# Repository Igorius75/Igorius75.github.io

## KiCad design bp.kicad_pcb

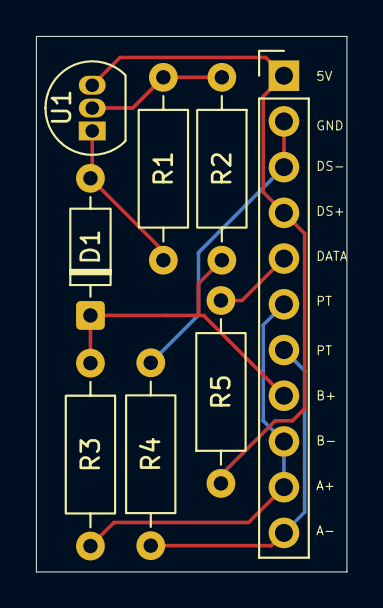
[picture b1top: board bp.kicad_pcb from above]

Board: 2 copper layers, 17.2 x 29.8 mm, 8 parts (0 on the bottom side), 8 nets.

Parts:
D1: 1N4148; D_DO-35_SOD27_P7.62mm_Horizontal
J5: Conn_01x11; PinHeader_1x11_P2.54mm_Vertical
R1: 860; R_Axial_DIN0207_L6.3mm_D2.5mm_P10.16mm_Horizontal
R2: 11k; R_Axial_DIN0207_L6.3mm_D2.5mm_P10.16mm_Horizontal
R3: 100; R_Axial_DIN0207_L6.3mm_D2.5mm_P10.16mm_Horizontal
R4: 15k; R_Axial_DIN0207_L6.3mm_D2.5mm_P10.16mm_Horizontal
R5: 4.7k; R_Axial_DIN0207_L6.3mm_D2.5mm_P10.16mm_Horizontal
U1: LM334Z; TO-92_Inline

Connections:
A-: J5.7, J5.11, R4.1
B+: D1.1 (K), J5.8, R2.2, R3.1
B-/A+: J5.6, J5.9, J5.10, R3.2
unnamed: D1.2 (A), R1.2, U1.1
unnamed: J5.1, J5.4, R5.1, U1.3
unnamed: J5.2, J5.3, R4.2
unnamed: J5.5, R5.2
unnamed: R1.1, R2.1, U1.2

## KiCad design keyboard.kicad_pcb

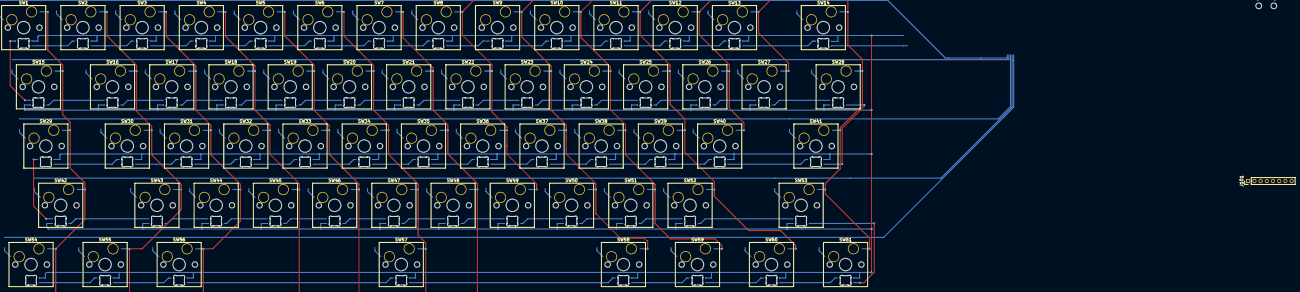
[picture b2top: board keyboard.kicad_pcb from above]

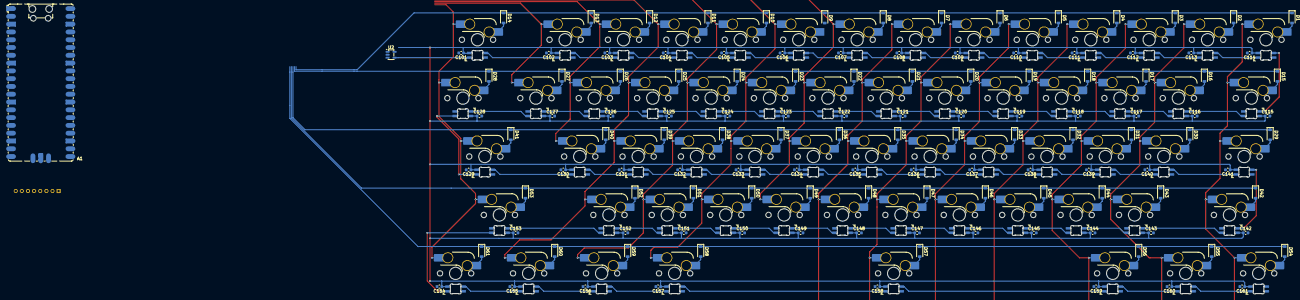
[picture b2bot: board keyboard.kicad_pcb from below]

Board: 2 copper layers, 247 parts (124 on the bottom side), 150 nets.

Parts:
A1: RaspberryPi_Pico; RaspberryPi_Pico_SMD_HandSolder
C101, C102, C103, C104, C105, C106, C107, C108, C109, C110, C111, C112, C113, C114, C115, C116, C117, C118, C119, C120, C121, C122, C123, C124, C125, C126, C127, C128, C129, C130, C131, C132, C133, C134, C135, C136, C137, C138, C139, C140, C141, C142, C143, C144, C145, C146, C147, C148, C149, C150, C151, C152, C153, C154, C155, C156, C157, C158, C159, C160, C161: 100nF; C_0603_1608Metric
D1, D2, D3, D4, D5, D6, D7, D8, D9, D10, D11, D12, D13, D14, D15, D16, D17, D18, D19, D20, D21, D22, D23, D24, D25, D26, D27, D28, D29, D30, D31, D32, D33, D34, D35, D36, D37, D38, D39, D40, D41, D42, D43, D44, D45, D46, D47, D48, D49, D50, D51, D52, D53, D54, D55, D56, D57, D58, D59, D60, D61: D; D_SOD-123
D101, D102, D103, D104, D105, D106, D107, D108, D109, D110, D111, D112, D113, D114, D129, D130, D131, D132, D133, D134, D135, D136, D137, D138, D139, D140, D141, D154, D155, D156, D157, D158, D159, D160, D161: SK6812MINI; MX_SK6812MINI-E
D115, D116, D117, D118, D119, D120, D121, D122, D123, D124, D125, D126, D127, D128, D142, D143, D144, D145, D146, D147, D148, D149, D150, D151, D152, D153: SK6812MINI; MX_SK6812MINI-E_REV
J101: ConnSPI; PinHeader_1x08_P2.00mm_Vertical
SW1, SW2, SW3, SW4, SW5, SW6, SW7, SW8, SW9, SW10, SW11, SW12, SW13, SW16, SW17, SW18, SW19, SW20, SW21, SW22, SW23, SW24, SW25, SW26, SW27, SW30, SW31, SW32, SW33, SW34, SW35, SW36, SW37, SW38, SW39, SW40, SW43, SW44, SW45, SW46, SW47, SW48, SW49, SW50, SW51, SW52: SW_Push; SW_Hotswap_Kailh_MX_Plated_1.00u
SW14: SW_Push; SW_Hotswap_Kailh_MX_Plated_2.00u
SW15, SW28: SW_Push; SW_Hotswap_Kailh_MX_Plated_1.50u
SW29: SW_Push; SW_Hotswap_Kailh_MX_Plated_1.75u
SW41, SW42: SW_Push; SW_Hotswap_Kailh_MX_Plated_2.25u
SW53: SW_Push; SW_Hotswap_Kailh_MX_Plated_2.75u
SW54, SW55, SW56, SW58, SW59, SW60, SW61: SW_Push; SW_Hotswap_Kailh_MX_Plated_1.25u
SW57: SW_Push; SW_Hotswap_Kailh_MX_Plated_6.25u
U2: SN74LV1T34DBV; SOT-23-5

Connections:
3V3: A1.36 (3V3), J101.1 (BLK), J101.7 (VCC)
C1: SW1.2, SW15.2, SW29.2, SW42.2, SW54.2
C2: SW2.2, SW16.2, SW30.2, SW43.2, SW55.2
C3: SW3.2, SW17.2, SW31.2, SW44.2, SW56.2
C4: SW4.2, SW18.2, SW32.2, SW45.2
C5: SW5.2, SW19.2, SW33.2, SW46.2
C6: SW6.2, SW20.2, SW34.2, SW47.2, SW57.2
C7: SW7.2, SW21.2, SW35.2, SW48.2
C8: SW8.2, SW22.2, SW36.2, SW49.2
C9: SW9.2, SW23.2, SW37.2, SW50.2, SW58.2
C10: SW10.2, SW24.2, SW38.2, SW51.2, SW59.2
C11: SW11.2, SW25.2, SW39.2, SW52.2, SW60.2
C12: SW12.2, SW26.2, SW40.2
C13: SW13.2, SW27.2
C14: SW14.2, SW28.2, SW41.2, SW53.2, SW61.2
GND: A1.3 (GND), A1.8 (GND), A1.13 (GND), A1.18 (GND), A1.23 (GND), A1.28 (GND), A1.38 (GND), A1.D2 (GND), C101.2, C102.2, C103.2, C104.2, C105.2, C106.2, C107.2, C108.2, C109.2, C110.2, C111.2, C112.2, C113.2, C114.2, C115.2, C116.2, C117.2, C118.2, C119.2, C120.2, C121.2, C122.2, C123.2, C124.2, C125.2, C126.2, C127.2, C128.2, C129.2, C130.2, C131.2, C132.2, C133.2, C134.2, C135.2, C136.2, C137.2, C138.2, C139.2, C140.2, C141.2, C142.2, C143.2, C144.2, C145.2, C146.2, C147.2, C148.2, C149.2, C150.2, C151.2, C152.2, C153.2, C154.2, C155.2, C156.2, C157.2, C158.2, C159.2, C160.2, C161.2, D101.2 (VSS), D102.2 (VSS), D103.2 (VSS), D104.2 (VSS), D105.2 (VSS), D106.2 (VSS), D107.2 (VSS), D108.2 (VSS), D109.2 (VSS), D110.2 (VSS), D111.2 (VSS), D112.2 (VSS), D113.2 (VSS), D114.2 (VSS), D115.2 (VSS), D116.2 (VSS), D117.2 (VSS), D118.2 (VSS), D119.2 (VSS), D120.2 (VSS), D121.2 (VSS), D122.2 (VSS), D123.2 (VSS), D124.2 (VSS), D125.2 (VSS), D126.2 (VSS), D127.2 (VSS), D128.2 (VSS), D129.2 (VSS), D130.2 (VSS), D131.2 (VSS), D132.2 (VSS), D133.2 (VSS), D134.2 (VSS), D135.2 (VSS), D136.2 (VSS), D137.2 (VSS), D138.2 (VSS), D139.2 (VSS), D140.2 (VSS), D141.2 (VSS), D142.2 (VSS), D143.2 (VSS), D144.2 (VSS), D145.2 (VSS), D146.2 (VSS), D147.2 (VSS), D148.2 (VSS), D149.2 (VSS), D150.2 (VSS), D151.2 (VSS), D152.2 (VSS), D153.2 (VSS), D154.2 (VSS), D155.2 (VSS), D156.2 (VSS), D157.2 (VSS), D158.2 (VSS), D159.2 (VSS), D160.2 (VSS), D161.2 (VSS), J101.8 (GND), U2.3 (GND)
LEDdata: D101.3 (DIN), U2.4 (Y)
unnamed: A1.12 (GPIO9), U2.2 (A)
unnamed: A1.14 (GPIO10), J101.6 (SCL)
unnamed: A1.15 (GPIO11), J101.5 (SDA)
unnamed: A1.16 (GPIO12), J101.3 (DC)
unnamed: A1.17 (GPIO13), J101.2 (CS)
unnamed: A1.19 (GPIO14), J101.4 (RES)
unnamed: D1.2 (A), SW1.1
unnamed: D2.2 (A), SW2.1
unnamed: D3.2 (A), SW3.1
unnamed: D4.2 (A), SW4.1
unnamed: D5.2 (A), SW5.1
unnamed: D6.2 (A), SW6.1
unnamed: D7.2 (A), SW7.1
unnamed: D8.2 (A), SW8.1
unnamed: D9.2 (A), SW9.1
unnamed: D10.2 (A), SW10.1
unnamed: D11.2 (A), SW11.1
unnamed: D12.2 (A), SW12.1
unnamed: D13.2 (A), SW13.1
unnamed: D14.2 (A), SW14.1
unnamed: D15.2 (A), SW15.1
unnamed: D16.2 (A), SW16.1
unnamed: D17.2 (A), SW17.1
unnamed: D18.2 (A), SW18.1
unnamed: D19.2 (A), SW19.1
unnamed: D20.2 (A), SW20.1
unnamed: D21.2 (A), SW21.1
unnamed: D22.2 (A), SW22.1
unnamed: D23.2 (A), SW23.1
unnamed: D24.2 (A), SW24.1
unnamed: D25.2 (A), SW25.1
unnamed: D26.2 (A), SW26.1
unnamed: D27.2 (A), SW27.1
unnamed: D28.2 (A), SW28.1
unnamed: D29.2 (A), SW29.1
unnamed: D30.2 (A), SW30.1
unnamed: D31.2 (A), SW31.1
unnamed: D32.2 (A), SW32.1
unnamed: D33.2 (A), SW33.1
unnamed: D34.2 (A), SW34.1
unnamed: D35.2 (A), SW35.1
unnamed: D36.2 (A), SW36.1
unnamed: D37.2 (A), SW37.1
unnamed: D38.2 (A), SW38.1
unnamed: D39.2 (A), SW39.1
unnamed: D40.2 (A), SW40.1
unnamed: D41.2 (A), SW41.1
unnamed: D42.2 (A), SW42.1
unnamed: D43.2 (A), SW43.1
unnamed: D44.2 (A), SW44.1
unnamed: D45.2 (A), SW45.1
unnamed: D46.2 (A), SW46.1
unnamed: D47.2 (A), SW47.1
unnamed: D48.2 (A), SW48.1
unnamed: D49.2 (A), SW49.1
unnamed: D50.2 (A), SW50.1
unnamed: D51.2 (A), SW51.1
unnamed: D52.2 (A), SW52.1
unnamed: D53.2 (A), SW53.1
unnamed: D54.2 (A), SW54.1
unnamed: D55.2 (A), SW55.1
unnamed: D56.2 (A), SW56.1
unnamed: D57.2 (A), SW57.1
unnamed: D58.2 (A), SW58.1
unnamed: D59.2 (A), SW59.1
unnamed: D60.2 (A), SW60.1
unnamed: D61.2 (A), SW61.1
unnamed: D101.1 (DOUT), D102.3 (DIN)
unnamed: D102.1 (DOUT), D103.3 (DIN)
unnamed: D103.1 (DOUT), D104.3 (DIN)
unnamed: D104.1 (DOUT), D105.3 (DIN)
unnamed: D105.1 (DOUT), D106.3 (DIN)
unnamed: D106.1 (DOUT), D107.3 (DIN)
unnamed: D107.1 (DOUT), D108.3 (DIN)
unnamed: D108.1 (DOUT), D109.3 (DIN)
unnamed: D109.1 (DOUT), D110.3 (DIN)
unnamed: D110.1 (DOUT), D111.3 (DIN)
unnamed: D111.1 (DOUT), D112.3 (DIN)
unnamed: D112.1 (DOUT), D113.3 (DIN)
unnamed: D113.1 (DOUT), D114.3 (DIN)
unnamed: D114.1 (DOUT), D115.3 (DIN)
unnamed: D115.1 (DOUT), D116.3 (DIN)
unnamed: D116.1 (DOUT), D117.3 (DIN)
unnamed: D117.1 (DOUT), D118.3 (DIN)
unnamed: D118.1 (DOUT), D119.3 (DIN)
unnamed: D119.1 (DOUT), D120.3 (DIN)
unnamed: D120.1 (DOUT), D121.3 (DIN)
unnamed: D121.1 (DOUT), D122.3 (DIN)
unnamed: D122.1 (DOUT), D123.3 (DIN)
unnamed: D123.1 (DOUT), D124.3 (DIN)
unnamed: D124.1 (DOUT), D125.3 (DIN)
unnamed: D125.1 (DOUT), D126.3 (DIN)
unnamed: D126.1 (DOUT), D127.3 (DIN)
unnamed: D127.1 (DOUT), D128.3 (DIN)
unnamed: D128.1 (DOUT), D129.3 (DIN)
unnamed: D129.1 (DOUT), D130.3 (DIN)
unnamed: D130.1 (DOUT), D131.3 (DIN)
unnamed: D131.1 (DOUT), D132.3 (DIN)
unnamed: D132.1 (DOUT), D133.3 (DIN)
unnamed: D133.1 (DOUT), D134.3 (DIN)
unnamed: D134.1 (DOUT), D135.3 (DIN)
unnamed: D135.1 (DOUT), D136.3 (DIN)
unnamed: D136.1 (DOUT), D137.3 (DIN)
unnamed: D137.1 (DOUT), D138.3 (DIN)
unnamed: D138.1 (DOUT), D139.3 (DIN)
unnamed: D139.1 (DOUT), D140.3 (DIN)
unnamed: D140.1 (DOUT), D141.3 (DIN)
unnamed: D141.1 (DOUT), D142.3 (DIN)
unnamed: D142.1 (DOUT), D143.3 (DIN)
unnamed: D143.1 (DOUT), D144.3 (DIN)
unnamed: D144.1 (DOUT), D145.3 (DIN)
unnamed: D145.1 (DOUT), D146.3 (DIN)
unnamed: D146.1 (DOUT), D147.3 (DIN)
unnamed: D147.1 (DOUT), D148.3 (DIN)
unnamed: D148.1 (DOUT), D149.3 (DIN)
unnamed: D149.1 (DOUT), D150.3 (DIN)
unnamed: D150.1 (DOUT), D151.3 (DIN)
unnamed: D151.1 (DOUT), D152.3 (DIN)
unnamed: D152.1 (DOUT), D153.3 (DIN)
unnamed: D153.1 (DOUT), D154.3 (DIN)
unnamed: D154.1 (DOUT), D155.3 (DIN)
unnamed: D155.1 (DOUT), D156.3 (DIN)
unnamed: D156.1 (DOUT), D157.3 (DIN)
unnamed: D157.1 (DOUT), D158.3 (DIN)
unnamed: D158.1 (DOUT), D159.3 (DIN)
unnamed: D159.1 (DOUT), D160.3 (DIN)
unnamed: D160.1 (DOUT), D161.3 (DIN)
R1: D1.1 (K), D2.1 (K), D3.1 (K), D4.1 (K), D5.1 (K), D6.1 (K), D7.1 (K), D8.1 (K), D9.1 (K), D10.1 (K), D11.1 (K), D12.1 (K), D13.1 (K), D14.1 (K)
R2: D15.1 (K), D16.1 (K), D17.1 (K), D18.1 (K), D19.1 (K), D20.1 (K), D21.1 (K), D22.1 (K), D23.1 (K), D24.1 (K), D25.1 (K), D26.1 (K), D27.1 (K), D28.1 (K)
R3: D29.1 (K), D30.1 (K), D31.1 (K), D32.1 (K), D33.1 (K), D34.1 (K), D35.1 (K), D36.1 (K), D37.1 (K), D38.1 (K), D39.1 (K), D40.1 (K), D41.1 (K)
R4: D42.1 (K), D43.1 (K), D44.1 (K), D45.1 (K), D46.1 (K), D47.1 (K), D48.1 (K), D49.1 (K), D50.1 (K), D51.1 (K), D52.1 (K), D53.1 (K)
R5: D54.1 (K), D55.1 (K), D56.1 (K), D57.1 (K), D58.1 (K), D59.1 (K), D60.1 (K), D61.1 (K)
Vсс: A1.40 (VBUS), C101.1, C102.1, C103.1, C104.1, C105.1, C106.1, C107.1, C108.1, C109.1, C110.1, C111.1, C112.1, C113.1, C114.1, C115.1, C116.1, C117.1, C118.1, C119.1, C120.1, C121.1, C122.1, C123.1, C124.1, C125.1, C126.1, C127.1, C128.1, C129.1, C130.1, C131.1, C132.1, C133.1, C134.1, C135.1, C136.1, C137.1, C138.1, C139.1, C140.1, C141.1, C142.1, C143.1, C144.1, C145.1, C146.1, C147.1, C148.1, C149.1, C150.1, C151.1, C152.1, C153.1, C154.1, C155.1, C156.1, C157.1, C158.1, C159.1, C160.1, C161.1, D101.4 (VDD), D102.4 (VDD), D103.4 (VDD), D104.4 (VDD), D105.4 (VDD), D106.4 (VDD), D107.4 (VDD), D108.4 (VDD), D109.4 (VDD), D110.4 (VDD), D111.4 (VDD), D112.4 (VDD), D113.4 (VDD), D114.4 (VDD), D115.4 (VDD), D116.4 (VDD), D117.4 (VDD), D118.4 (VDD), D119.4 (VDD), D120.4 (VDD), D121.4 (VDD), D122.4 (VDD), D123.4 (VDD), D124.4 (VDD), D125.4 (VDD), D126.4 (VDD), D127.4 (VDD), D128.4 (VDD), D129.4 (VDD), D130.4 (VDD), D131.4 (VDD), D132.4 (VDD), D133.4 (VDD), D134.4 (VDD), D135.4 (VDD), D136.4 (VDD), D137.4 (VDD), D138.4 (VDD), D139.4 (VDD), D140.4 (VDD), D141.4 (VDD), D142.4 (VDD), D143.4 (VDD), D144.4 (VDD), D145.4 (VDD), D146.4 (VDD), D147.4 (VDD), D148.4 (VDD), D149.4 (VDD), D150.4 (VDD), D151.4 (VDD), D152.4 (VDD), D153.4 (VDD), D154.4 (VDD), D155.4 (VDD), D156.4 (VDD), D157.4 (VDD), D158.4 (VDD), D159.4 (VDD), D160.4 (VDD), D161.4 (VDD), U2.5 (VCC)

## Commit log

2018-05-23 init commit
2018-05-23 Create CNAME
